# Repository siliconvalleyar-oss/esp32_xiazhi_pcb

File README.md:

# XiaoZhi - Asistente de Voz con ESP32-C6 (Versión Multisensor)

Repositorio del diseño PCB para el dispositivo **XiaoZhi**, una estación de desarrollo y asistente de voz de código abierto basado en el **ESP32-C6**. Este diseño integra audio digital de alta calidad, iluminación RGB, pantalla OLED, **pantalla TFT**, **sensores ambientales (gas, temperatura/humedad, distancia)** y **comunicación CAN** en una sola placa diseñada con **KiCad**.

---

## 📖 Descripción

XiaoZhi evoluciona para convertirse en un nodo IoT multisensor ideal para automatización del hogar, monitoreo industrial o robótica. Además de la interacción por voz (micrófono y altavoz), la placa incorpora:

- **MQ-6**: Detección de gases combustibles (LPG, butano, metano).
- **AHT21B**: Medición precisa de temperatura y humedad ambiental (I2C).
- **VL53L0X**: Sensor de distancia por tiempo de vuelo (ToF) de hasta 2 metros.
- **ST7789**: Pantalla TFT a color para gráficos avanzados (SPI).
- **MCP2515**: Controlador CAN bus (con transceptor) para comunicación vehicular o industrial.

Todo ello manteniendo la conectividad Wi-Fi 6, BLE 5.0 y la interfaz USB-UART integrada.

---

## ✨ Características Principales

- **Microcontrolador**: ESP32-C6 (RISC-V dual-core, Wi-Fi 6, BLE 5.0, Zigbee/Thread).
- **Audio**:
  - Micrófono MEMS **INMP441** (I2S).
  - Amplificador **MAX98357A** (I2S) para altavoz externo.
- **Interfaz y depuración**: **FT232** integrado para USB-UART.
- **Iluminación y control**:
  - LED GPIO estándar y LED direccionable **WS2812**.
  - Pulsadores (BOOT y RESET).
- **Pantallas**:
  - **SSD1306** (OLED 128x64, I2C) para información rápida.
  - **ST7789** (TFT a color, SPI) para gráficos, menús o visualización de datos.
- **Sensores**:
  - **MQ-6** (gas) – Salida analógica (ADC).
  - **AHT21B** (temperatura/humedad) – I2C.
  - **VL53L0X** (distancia ToF) – I2C.
- **Comunicación industrial**:
  - **MCP2515** + transceptor CAN (SPI) para bus CAN 2.0.
- **Alimentación**: 5V vía USB-C, con reguladores internos para 3.3V.

---

## 📦 Lista de Componentes (BOM)

| Componente | Cantidad | Descripción | Referencia en PCB |
| :--- | :--- | :--- | :--- |
| ESP32-C6-WROOM-1 | 1 | Módulo Wi-Fi/BLE/Zigbee | U1 |
| INMP441 | 1 | Micrófono MEMS I2S | U2 |
| MAX98357A | 1 | Amplificador Clase D I2S | U3 |
| FT232RL (o FT232RQ) | 1 | Conversor USB-UART | U4 |
| WS2812B | 1 (o N) | LED RGB direccionable | D1 |
| LED (GPIO) | 1 | LED indicador estándar | D2 |
| SWITCH (Push Button) | 2 | Pulsadores (BOOT y RESET) | SW1, SW2 |
| SSD1306 (I2C) | 1 | Display OLED de 0.96" | OLED1 |
| **MQ-6** | **1** | **Sensor de gas (LPG, butano, metano)** | **U6** |
| **AHT21B** | **1** | **Sensor de temperatura y humedad (I2C)** | **U7** |
| **VL53L0X** | **1** | **Sensor de distancia ToF (Time-of-Flight)** | **U8** |
| **ST7789** | **1** | **Pantalla TFT a color (SPI) - 1.3" / 1.54"** | **U9** |
| **MCP2515** | **1** | **Controlador CAN (SPI) + TJA1050 (transceptor)** | **U10** |
| Regulador 3.3V (AMS1117) | 1 | LDO para alimentación interna | U5 |
| Cristal 40MHz | 1 | Oscilador para FT232 (según esquema) | X1 |
| Resistencias, Capacitores, Conectores | Varios | Pasivos y terminales (USB-C, JST) | - |

---

## 🔌 Asignación de Pines (Pinout)

> **⚠️ Importante**: La siguiente tabla es una referencia estándar. Verifica siempre el esquemático (`*.sch`) para confirmar las conexiones finales.

| Periférico | Pin del ESP32-C6 | Descripción / Notas |
| :--- | :--- | :--- |
| **INMP441 (Mic)** | GPIO3 (I2S_BCK) | Bit Clock |
| | GPIO2 (I2S_WS) | Word Select (LRCLK) |
| | GPIO1 (I2S_DIN) | Data Output (DOUT) |
| | 3.3V / GND | Alimentación |
| **MAX98357A (Amp)** | GPIO3 (I2S_BCK) | Bit Clock (compartido) |
| | GPIO2 (I2S_WS) | Word Select (compartido) |
| | GPIO4 (I2S_DOUT) | Data Input (DIN) |
| | GPIO5 | Shutdown (SD) - Activo bajo |
| | 5V / GND | Alimentación |
| **WS2812** | GPIO6 | Data Input |
| | 5V / GND | Alimentación |
| **SSD1306 (OLED) / AHT21B / VL53L0X** | GPIO7 (I2C_SCL) | Bus I2C compartido (SCL) |
| | GPIO8 (I2C_SDA) | Bus I2C compartido (SDA) |
| | 3.3V / GND | Alimentación (todas comparten bus) |
| **FT232 (UART)** | GPIO9 (RX) | RX del ESP (conectar a TX del FT) |
| | GPIO10 (TX) | TX del ESP (conectar a RX del FT) |
| | GPIO11 (DTR) | Auto-reset (opcional) |
| **SWITCH BOOT** | GPIO12 | Boot (GPIO0 en otros chips, verificar) |
| **SWITCH RESET** | CHIP_EN | Reset (EN) |
| **LED GPIO** | GPIO13 | Ánodo del LED (con resistencia) |
| **MQ-6 (Gas)** | **GPIO14** | **Salida analógica (ADC)** |
| **ST7789 (TFT)** | **GPIO15 (SPI_MOSI)** | **Master Out / Slave In** |
| | **GPIO16 (SPI_SCLK)** | **Clock SPI** |
| | **GPIO17 (DC)** | **Data/Command** |
| | **GPIO18 (CS)** | **Chip Select (activo bajo)** |
| | **GPIO19 (RST)** | **Reset de la pantalla** |
| **MCP2515 (CAN)** | **GPIO15 (SPI_MOSI)** | **Comparte MOSI con TFT** |
| | **GPIO16 (SPI_SCLK)** | **Comparte SCLK con TFT** |
| | **GPIO20 (CS)** | **Chip Select exclusivo para CAN** |
| | **GPIO21 (INT)** | **Interrupción del MCP2515** |
| | 5V / GND | Alimentación (transceptor CAN) |

---

## 🧩 Integración de Sensores y Bus Compartido

Para optimizar los pines del ESP32-C6, el diseño utiliza buses compartidos:

- **Bus I2C (GPIO7 y GPIO8)**: Conecta simultáneamente el **SSD1306**, el **AHT21B** y el **VL53L0X**. Cada dispositivo tiene una dirección I2C única, por lo que no hay conflicto.
- **Bus SPI (GPIO15 y GPIO16)**: Conecta el **ST7789** y el **MCP2515**. Se diferencian mediante pines **CS (Chip Select)** independientes (GPIO18 para TFT, GPIO20 para CAN).
- **ADC (GPIO14)**: Reservado exclusivamente para la salida analógica del sensor de gas **MQ-6**. Se recomienda agregar un capacitor de filtrado en la PCB para estabilizar la lectura.

---

## 🛠️ Uso del Proyecto en KiCad

### Requisitos
- KiCad **v8.0** o superior.
- Símbolos y huellas adicionales para los nuevos componentes (es posible que necesites descargar librerías externas para el MCP2515, VL53L0X o ST7789).

### Abrir y Editar
1. Clona este repositorio:
   ```bash
   git clone https://github.com/tu-usuario/xiaozhi-pcb.git
   cd xiaozhi-pcb

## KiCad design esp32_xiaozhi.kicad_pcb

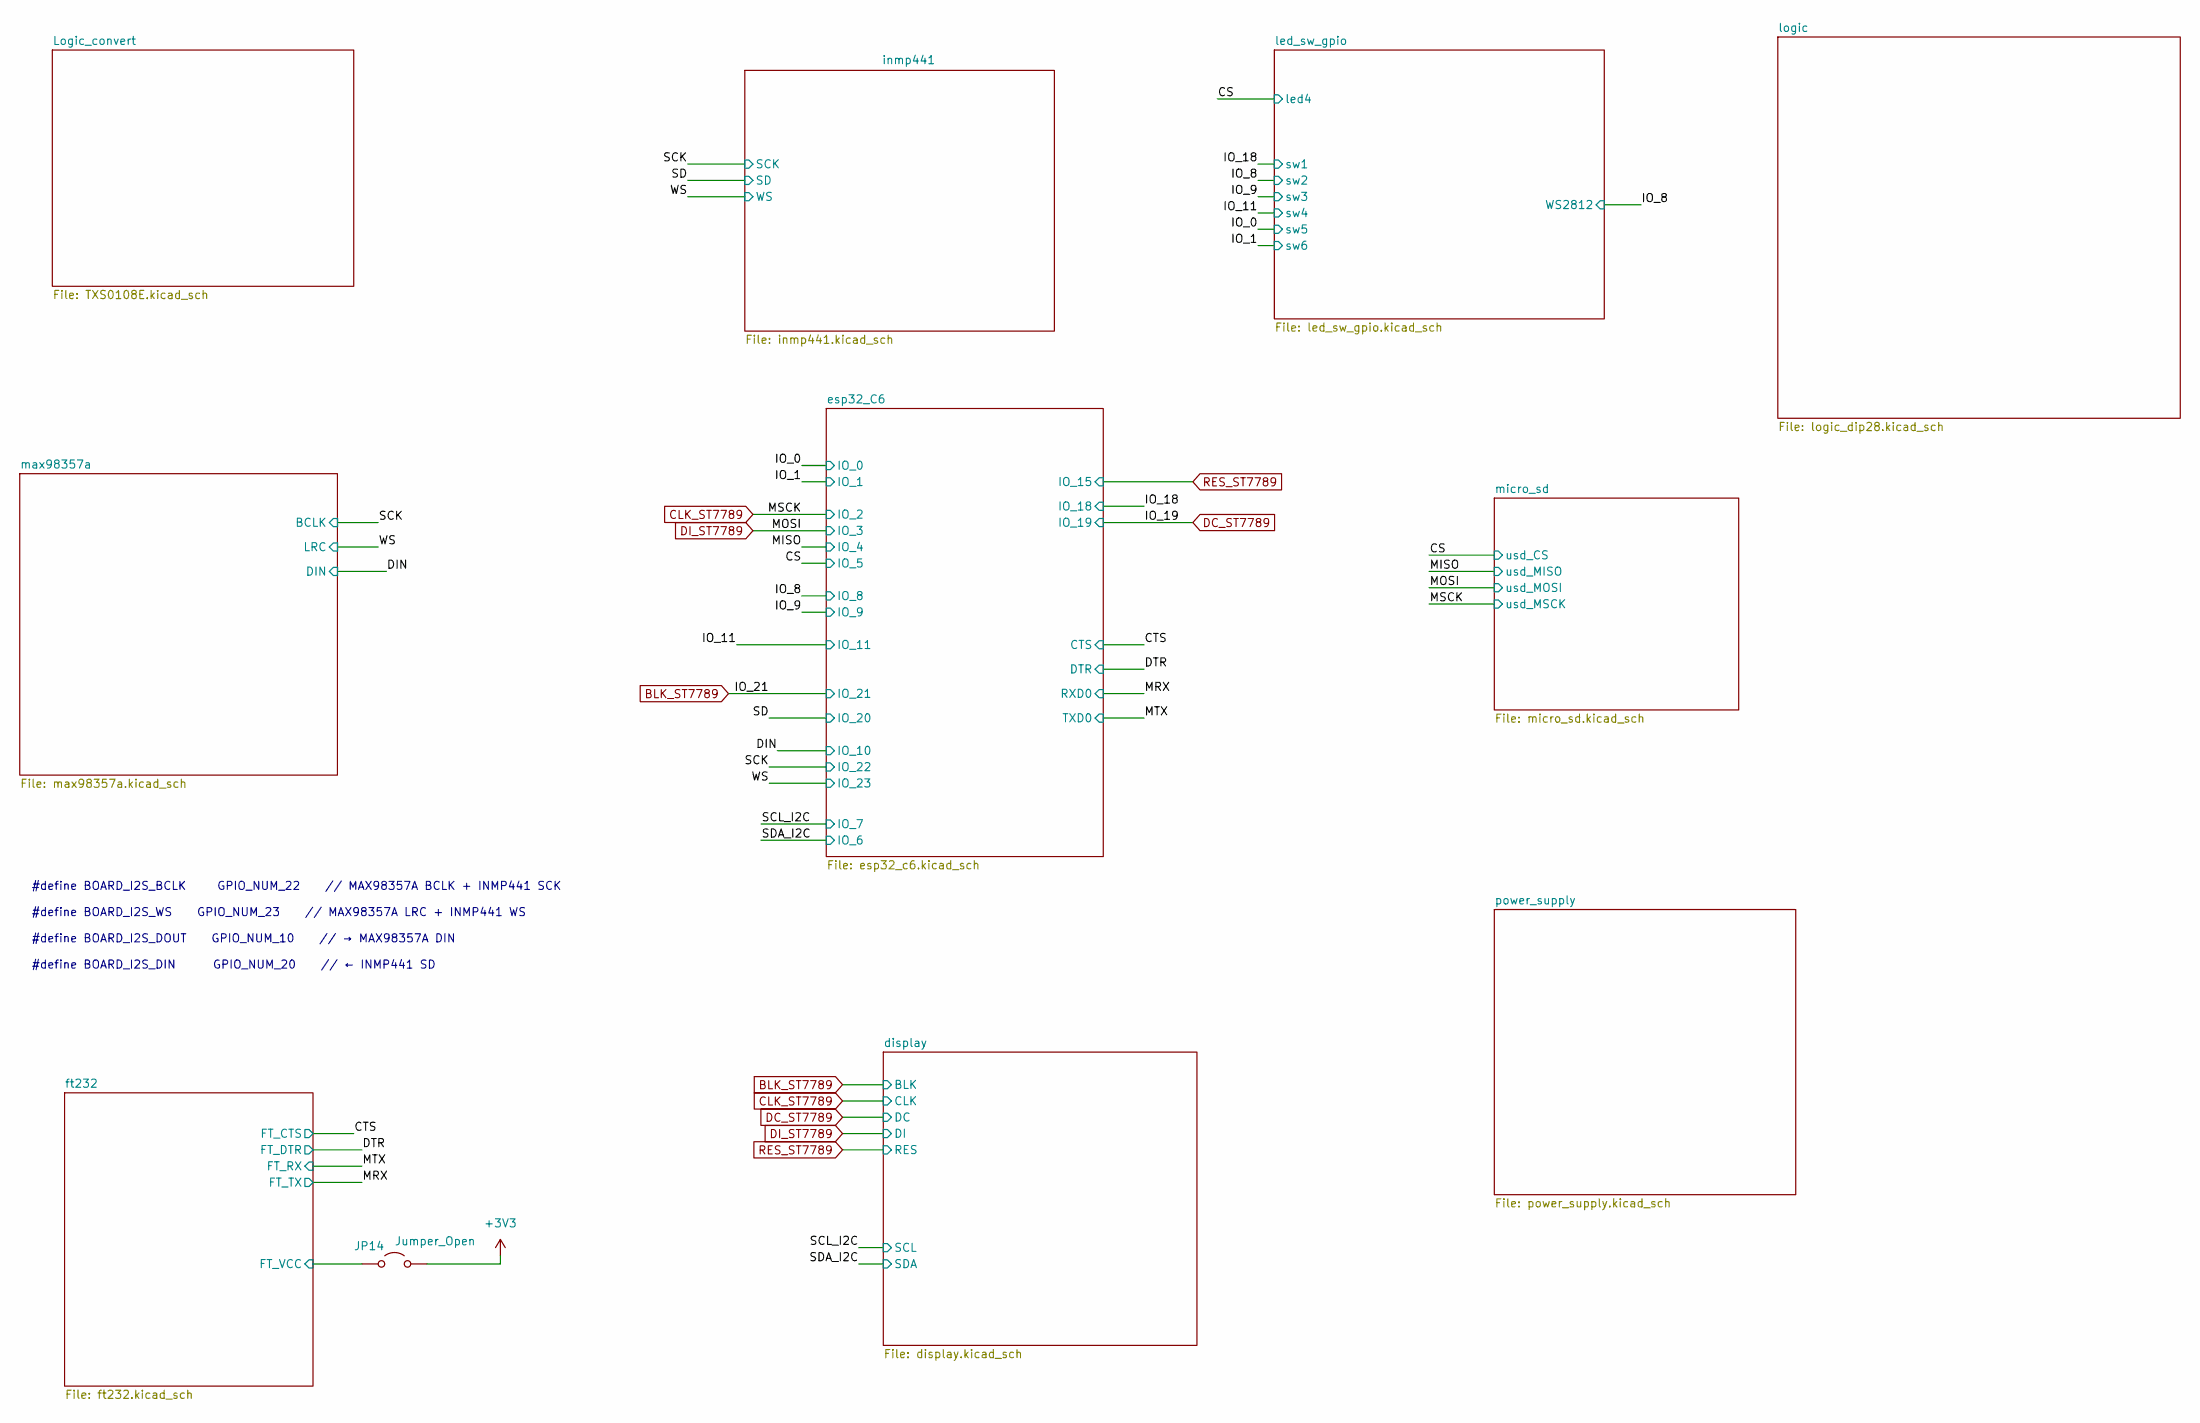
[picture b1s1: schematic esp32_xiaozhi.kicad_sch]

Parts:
JP14: Jumper_Open; SolderJumper-2_P1.3mm_Open_RoundedPad1.0x1.5mm

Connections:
+3V3: JP14.2 (B); also elsewhere on the board
+5VA: JP14.1 (A); also elsewhere on the board

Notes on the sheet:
#define BOARD_I2S_BCLK GPIO_NUM_22 // MAX98357A BCLK + INMP441 SCK #define BOARD_I2S_WS GPIO_NUM_23 // MAX98357A LRC + INMP441 WS #define BOARD_I2S_DOUT GPIO_NUM_10 // → MAX98357A DIN #define BOARD_I2S_DIN GPIO_NUM_20 // ← INMP441 SD

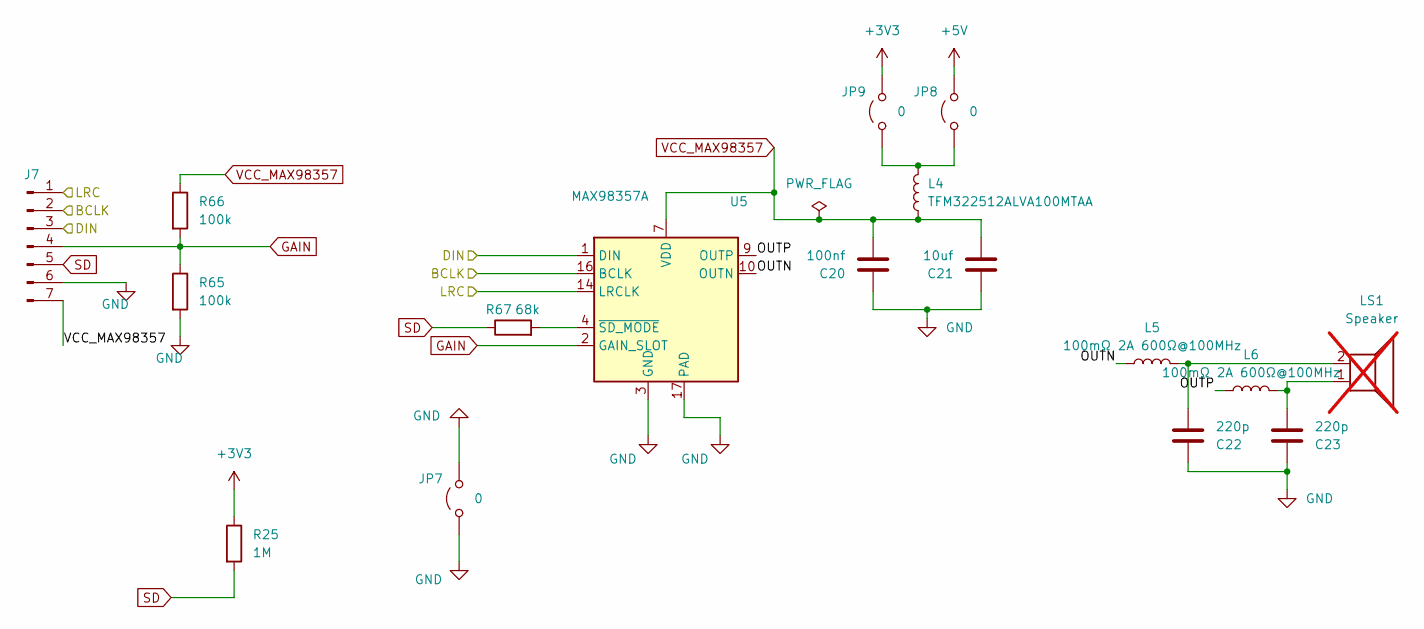
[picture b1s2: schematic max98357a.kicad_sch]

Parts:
C20: 100nf; C_0805_2012Metric; LCSC C28233
C21: 10uf; C_0805_2012Metric; LCSC C15850
C22, C23: 220p; C_0805_2012Metric; LCSC C107145
J7: PinHeader_1x07_P2.54mm_Vertical
JP7, JP8: 0; SolderJumper-2_P1.3mm_Bridged_RoundedPad1.0x1.5mm
JP9: 0; SolderJumper-2_P1.3mm_Open_RoundedPad1.0x1.5mm
L4: TFM322512ALVA100MTAA; L_1210_3225Metric; LCSC C1882517
L5, L6: 100mΩ 2A 600Ω@100MHz; L_0805_2012Metric; LCSC C845118
LS1: Speaker; Molex_Micro-Latch_53253-0270_1x02_P2.00mm_Vertical; not fitted
R25: 1M; R_0805_2012Metric; LCSC C17514
R65, R66: 100k; R_0805_2012Metric; LCSC C149504
R67: 68k; R_0805_2012Metric; LCSC C17801
U5: MAX98357A; TQFN-16-1EP_3x3mm_P0.5mm_EP1.23x1.23mm; LCSC C910544

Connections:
+3V3: JP9.2 (B), R25.1; also elsewhere on the board
+5V: JP8.2 (B); also elsewhere on the board
/DIN: J7.3, U5.1 (DIN); also elsewhere on the board
/SCK: J7.2, U5.16 (BCLK); also elsewhere on the board
/WS: J7.1, U5.14 (LRCLK); also elsewhere on the board
/max98357a/OUTN: L5.1, U5.10 (OUTN)
/max98357a/OUTP: L6.1, U5.9 (OUTP)
GAIN: J7.4, R65.1, R66.2, U5.2 (GAIN_SLOT)
unnamed: C22.2, L5.2, LS1.2
unnamed: C23.2, L6.2, LS1.1
unnamed: JP8.1 (A), JP9.1 (A), L4.2
unnamed: R67.2, U5.4 (~SD_MODE)
SD: J7.5, R25.2, R67.1
VCC_MAX98357: C20.2, C21.2, J7.7, L4.1, R66.1, U5.7 (VDD), U5.8 (VDD)

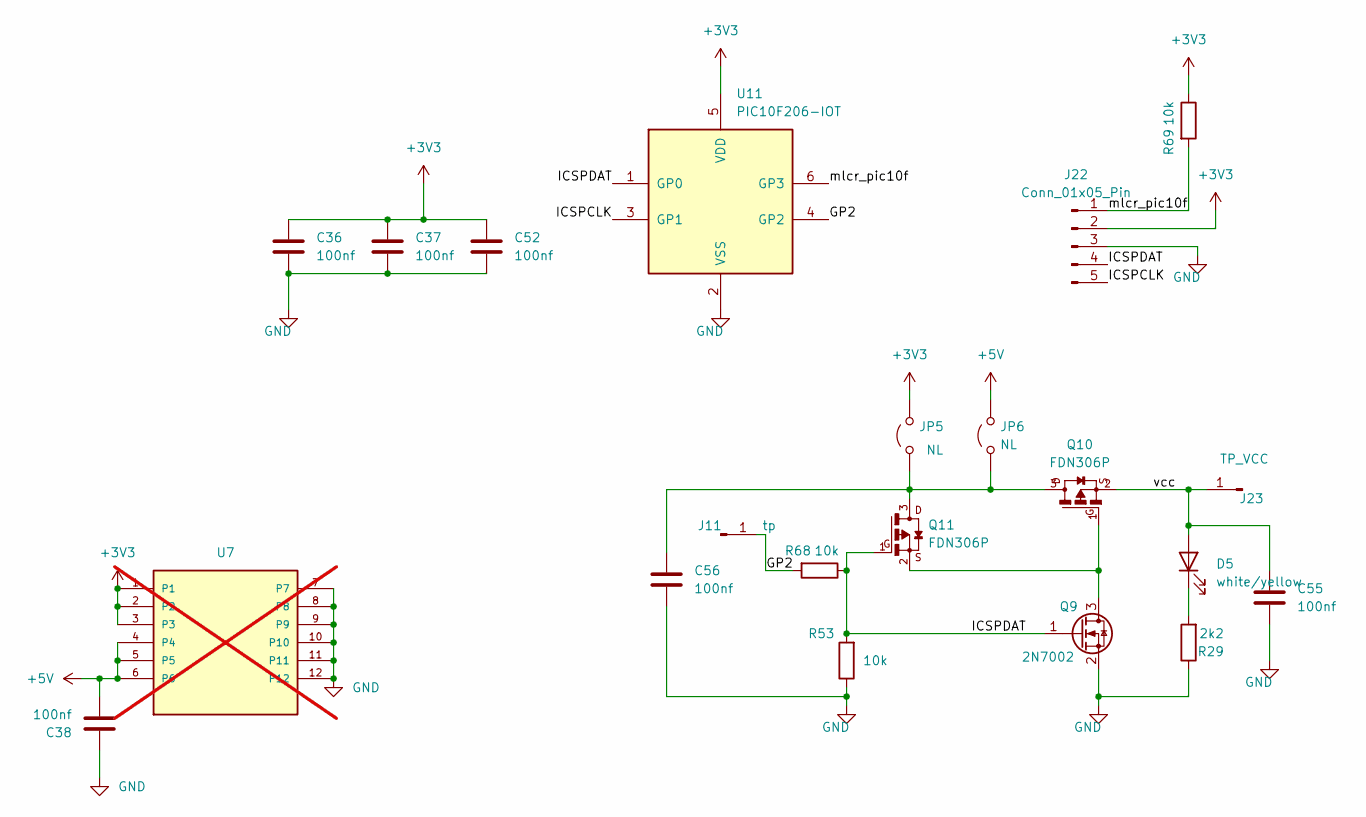
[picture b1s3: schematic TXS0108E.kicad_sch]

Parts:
C36, C37, C38, C52, C55, C56: 100nf; C_0805_2012Metric; LCSC C28233
D5: white/yellow; D_0805_2012Metric; LCSC C34499
J11: tp; TestPoint_Pad_D1.5mm
J22: Conn_01x05_Pin; PinHeader_1x06_P1.00mm_Vertical_SMD_Pin1Left
J23: TP_VCC; TestPoint_THTPad_1.0x1.0mm_Drill0.5mm
JP5, JP6: NL; SolderJumper-2_P1.3mm_Open_RoundedPad1.0x1.5mm
Q9: 2N7002; SOT-23; LCSC C8545
Q10, Q11: FDN306P; SOT-23W; LCSC C5236682
R29: 2k2; R_0805_2012Metric; LCSC C17520
R53, R68, R69: 10k; R_0805_2012Metric; LCSC C17414
U7: FMINI_PB_6X6; not fitted
U11: PIC10F206-IOT; SOT-23-6; LCSC C220623

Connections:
+3V3: C36.1, C37.1, C52.1, J22.2, JP5.2 (B), R69.1, U7.1, U7.2, U7.3, U11.5 (VDD); also elsewhere on the board
+5V: C38.2, JP6.2 (B), U7.4, U7.5, U7.6; also elsewhere on the board
/Logic_convert/GP2: J11.1 (Pin_1_1), R68.2, U11.4 (GP2)
/Logic_convert/ICSPCLK: J22.5, U11.3 (GP1)
/Logic_convert/ICSPDAT: J22.4, Q9.1 (G), Q11.1, R53.2, R68.1, U11.1 (GP0)
/Logic_convert/mlcr_pic10f: J22.1, R69.2, U11.6 (GP3)
/Logic_convert/vcc: C55.1, D5.2 (A), J23.1 (Pin_1_1), Q10.2
unnamed: D5.1 (K), R29.2
unnamed: C56.1, JP5.1 (A), JP6.1 (A), Q10.3, Q11.3
unnamed: Q9.3 (D), Q10.1, Q11.2

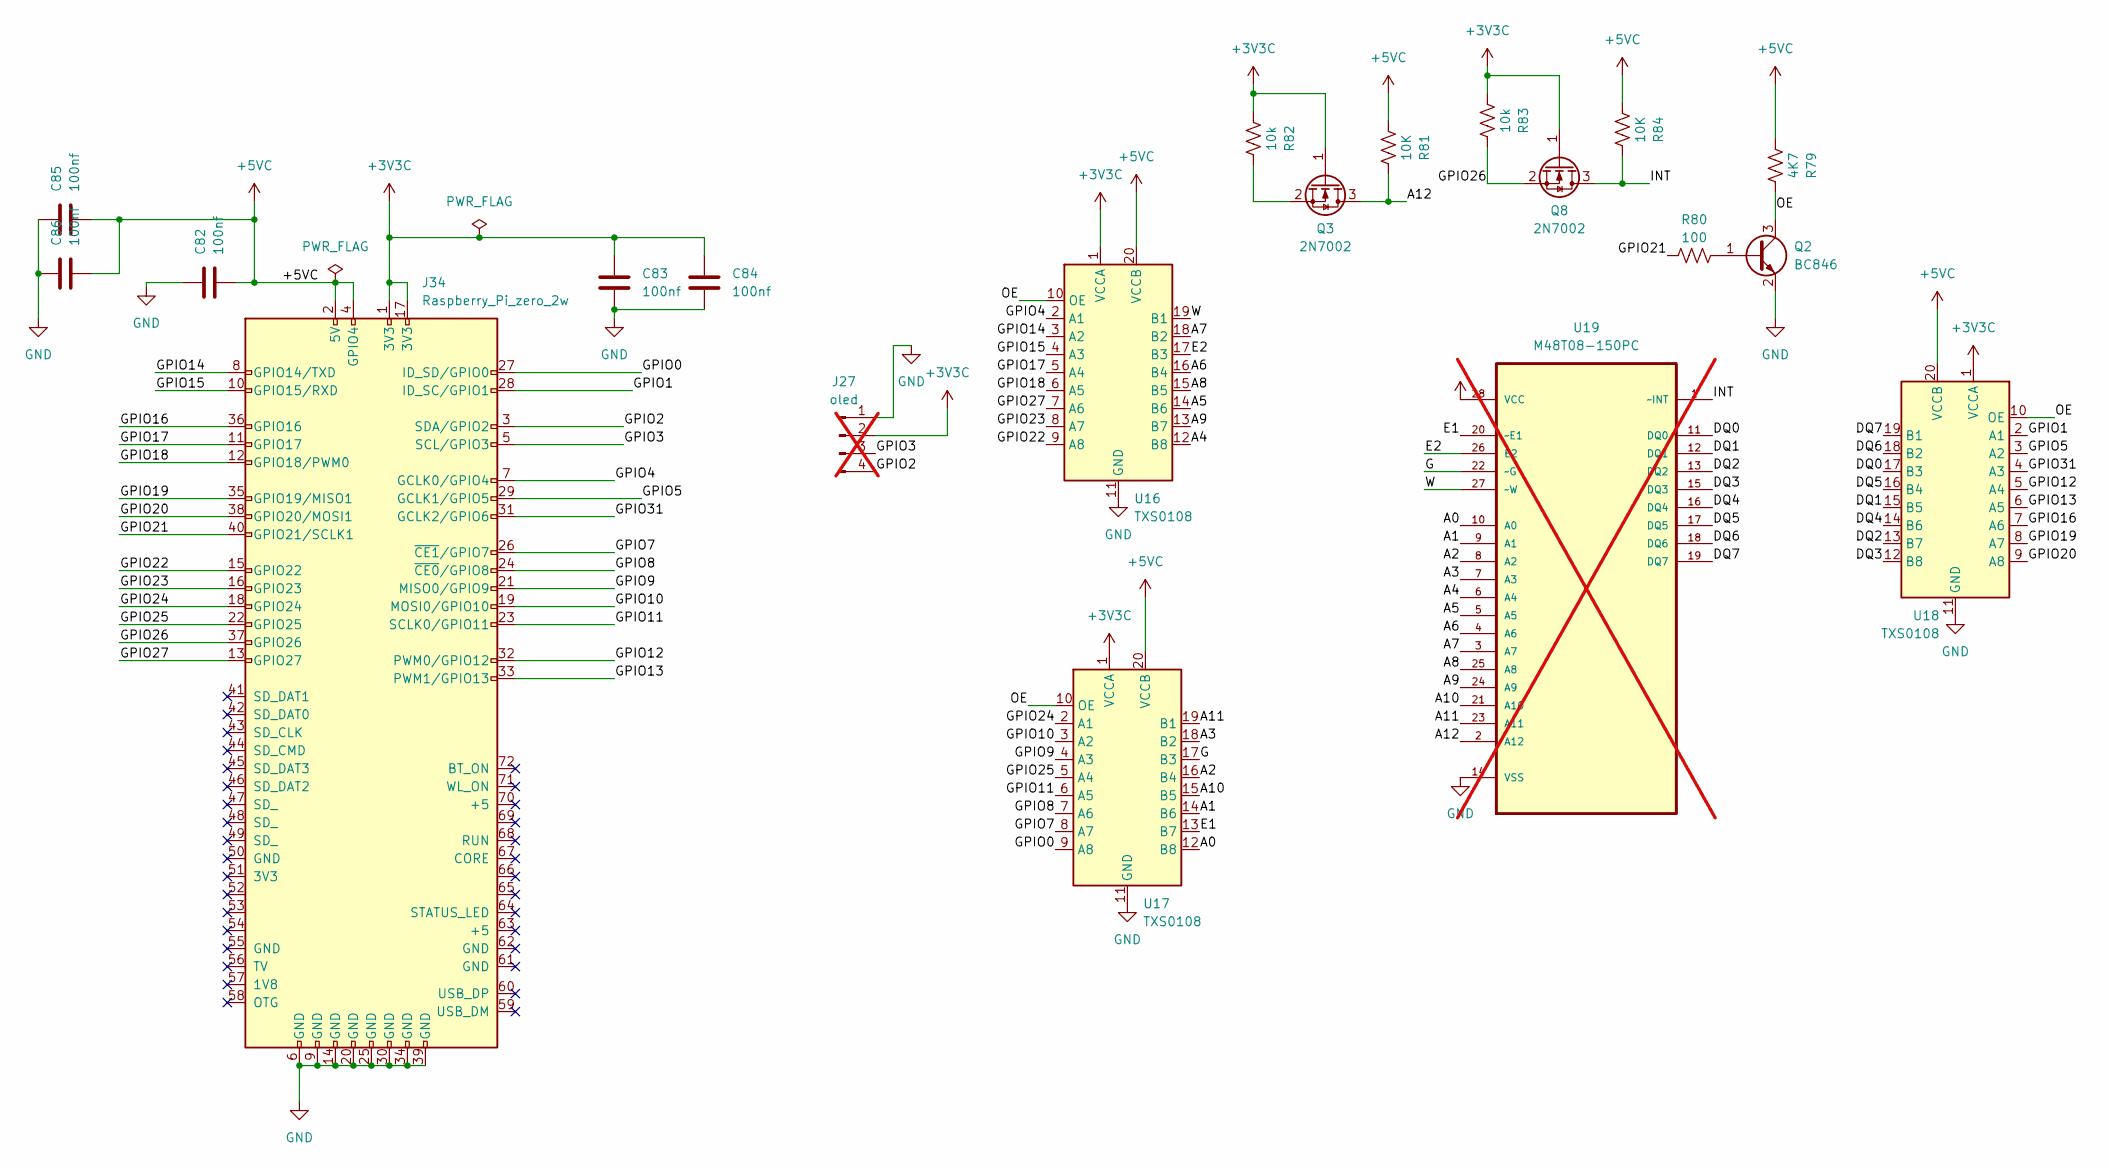
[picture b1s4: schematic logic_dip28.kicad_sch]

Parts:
C82, C85, C86: 100nf; C_0805_2012Metric
C83, C84: 100nf; C_0603_1608Metric
J27: oled; PinHeader_1x04_P2.54mm_Vertical; not fitted
J34: Raspberry_Pi_zero_2w; PinSocket_2x20_P2.54mm_Vertical_SMD
Q2: BC846; SOT-23
Q3, Q8: 2N7002; SOT-23
R79: 4K7; R_0603_1608Metric
R80: 100; R_0603_1608Metric
R81, R84: 10K; R_0603_1608Metric
R82, R83: 10k; R_0603_1608Metric
U16, U17, U18: TXS0108; TSSOP-20_4.4x6.5mm_P0.65mm
U19: M48T08-150PC; DIP-28_W15.24mm; MPN M48T08-150PC; not fitted

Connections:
+3V3C: C83.1, C84.1, J27.2, J34.1 (3V3), J34.17 (3V3), Q3.1 (G), Q8.1 (G), R82.1, R83.1, U16.1 (VCCA), U17.1 (VCCA), U18.1 (VCCA)
+5VC: C82.2, C85.2, C86.2, J34.2 (5V), J34.4 (GPIO4), R79.1, R81.1, R84.1, U16.20 (VCCB), U17.20 (VCCB), U18.20 (VCCB), U19.28 (VCC)
/logic/A0: U17.12 (B8), U19.10 (A0)
/logic/A1: U17.14 (B6), U19.9 (A1)
/logic/A2: U17.16 (B4), U19.8 (A2)
/logic/A3: U17.18 (B2), U19.7 (A3)
/logic/A4: U16.12 (B8), U19.6 (A4)
/logic/A5: U16.14 (B6), U19.5 (A5)
/logic/A6: U16.16 (B4), U19.4 (A6)
/logic/A7: U16.18 (B2), U19.3 (A7)
/logic/A8: U16.15 (B5), U19.25 (A8)
/logic/A9: U16.13 (B7), U19.24 (A9)
/logic/A10: U17.15 (B5), U19.21 (A10)
/logic/A11: U17.19 (B1), U19.23 (A11)
/logic/A12: Q3.3 (D), R81.2, U19.2 (A12)
/logic/DQ0: U18.17 (B3), U19.11 (DQ0)
/logic/DQ1: U18.15 (B5), U19.12 (DQ1)
/logic/DQ2: U18.13 (B7), U19.13 (DQ2)
/logic/DQ3: U18.12 (B8), U19.15 (DQ3)
/logic/DQ4: U18.14 (B6), U19.16 (DQ4)
/logic/DQ5: U18.16 (B4), U19.17 (DQ5)
/logic/DQ6: U18.18 (B2), U19.18 (DQ6)
/logic/DQ7: U18.19 (B1), U19.19 (DQ7)
/logic/E1: U17.13 (B7), U19.20 (~E1)
/logic/E2: U16.17 (B3), U19.26 (E2)
/logic/G: U17.17 (B3), U19.22 (~G)
/logic/GPIO0: J34.27 (ID_SD/GPIO0), U17.9 (A8)
/logic/GPIO1: J34.28 (ID_SC/GPIO1), U18.2 (A1)
/logic/GPIO2: J27.4, J34.3 (SDA/GPIO2)
/logic/GPIO3: J27.3, J34.5 (SCL/GPIO3)
/logic/GPIO4: J34.7 (GCLK0/GPIO4), U16.2 (A1)
/logic/GPIO5: J34.29 (GCLK1/GPIO5), U18.3 (A2)
/logic/GPIO7: J34.26 (~CE1/GPIO7), U17.8 (A7)
/logic/GPIO8: J34.24 (~CE0/GPIO8), U17.7 (A6)
/logic/GPIO9: J34.21 (MISO0/GPIO9), U17.4 (A3)
/logic/GPIO10: J34.19 (MOSI0/GPIO10), U17.3 (A2)
/logic/GPIO11: J34.23 (SCLK0/GPIO11), U17.6 (A5)
/logic/GPIO12: J34.32 (PWM0/GPIO12), U18.5 (A4)
/logic/GPIO13: J34.33 (PWM1/GPIO13), U18.6 (A5)
/logic/GPIO14: J34.8 (GPIO14/TXD), U16.3 (A2)
/logic/GPIO15: J34.10 (GPIO15/RXD), U16.4 (A3)
/logic/GPIO16: J34.36 (GPIO16), U18.7 (A6)
/logic/GPIO17: J34.11 (GPIO17), U16.5 (A4)
/logic/GPIO18: J34.12 (GPIO18/PWM0), U16.6 (A5)
/logic/GPIO19: J34.35 (GPIO19/MISO1), U18.8 (A7)
/logic/GPIO20: J34.38 (GPIO20/MOSI1), U18.9 (A8)
/logic/GPIO21: J34.40 (GPIO21/SCLK1), R80.1
/logic/GPIO22: J34.15 (GPIO22), U16.9 (A8)
/logic/GPIO23: J34.16 (GPIO23), U16.8 (A7)
/logic/GPIO24: J34.18 (GPIO24), U17.2 (A1)
/logic/GPIO25: J34.22 (GPIO25), U17.5 (A4)
/logic/GPIO26: J34.37 (GPIO26), Q8.2 (S), R83.2
/logic/GPIO27: J34.13 (GPIO27), U16.7 (A6)
/logic/GPIO31: J34.31 (GCLK2/GPIO6), U18.4 (A3)
/logic/INT: Q8.3 (D), R84.2, U19.1 (~INT)
/logic/OE: Q2.3 (C), R79.2, U16.10 (OE), U17.10 (OE), U18.10 (OE)
/logic/W: U16.19 (B1), U19.27 (~W)
unnamed: Q2.1 (B), R80.2
unnamed: Q3.2 (S), R82.2

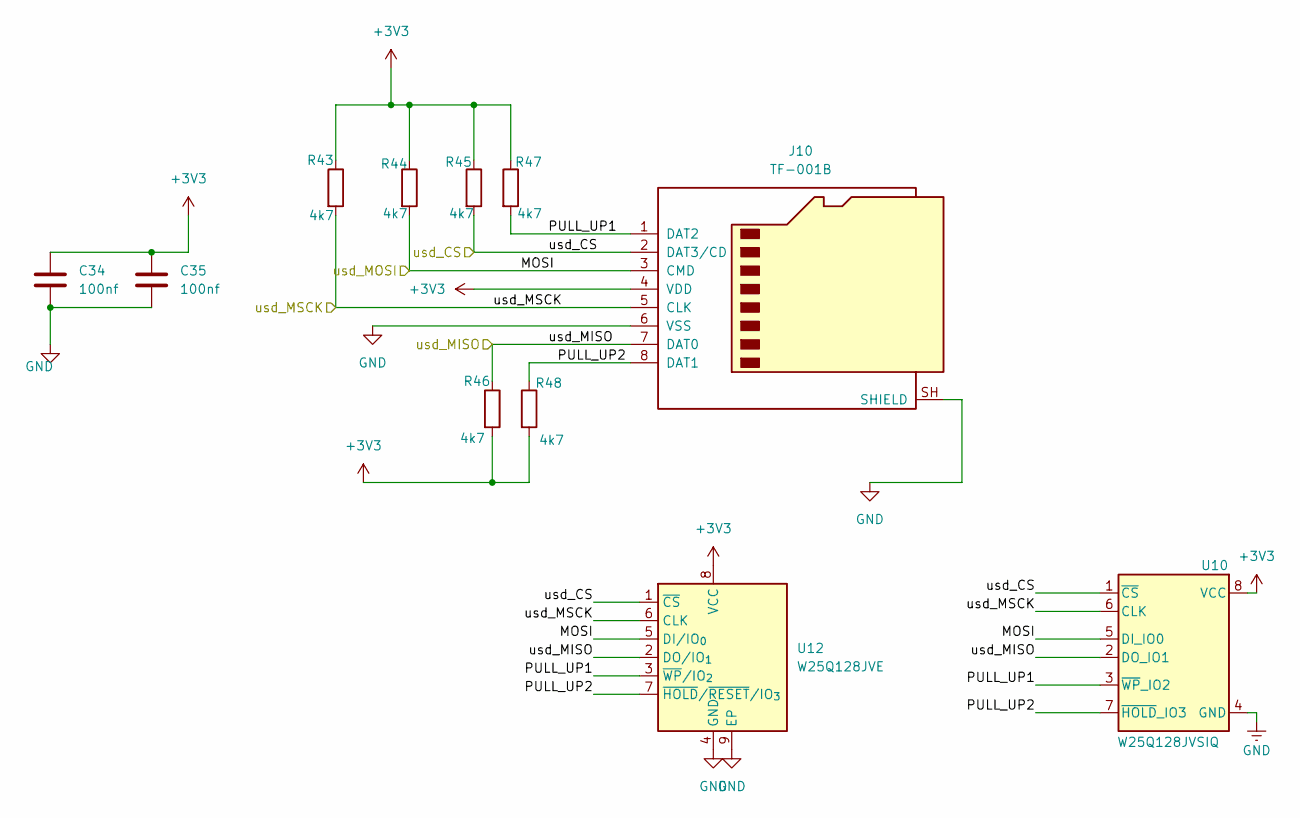
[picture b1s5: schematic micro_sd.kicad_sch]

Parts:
C34, C35: 100nf; C_0805_2012Metric; LCSC C28233
J10: TF-001B; LCSC C125617
R43, R44, R45, R46, R47, R48: 4k7; R_0805_2012Metric; LCSC C17673
U10: W25Q128JVSIQ; SOIC-8W_5.3x5.3mm_P1.27mm; voltage 2.7-3.6V; part_uid RP-01JWD4-F1H4N9; LCSC C97521
U12: W25Q128JVE; Winbond_XSON-8-1EP_4x4mm_P0.8mm_EP2.3x3.0mm

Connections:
+3V3: C34.1, C35.1, J10.4 (VDD), R43.1, R44.1, R45.1, R46.2, R47.1, R48.2, U10.8 (VCC), U12.8 (VCC); also elsewhere on the board
/CS: J10.2 (DAT3/CD), R45.2, U10.1 (~CS), U12.1 (~CS); also elsewhere on the board
/MISO: J10.7 (DAT0), R46.1, U10.2 (DO_IO1), U12.2 (DO/IO_{1}); also elsewhere on the board
/micro_sd/PULL_UP1: J10.1 (DAT2), R47.2, U10.3 (~WP_IO2), U12.3 (~WP/IO_{2})
/micro_sd/PULL_UP2: J10.8 (DAT1), R48.1, U10.7 (~HOLD_IO3), U12.7 (~HOLD/~RESET/IO_{3})
CLK_ST7789: J10.5 (CLK), R43.2, U10.6 (CLK), U12.6 (CLK); also elsewhere on the board
DI_ST7789: J10.3 (CMD), R44.2, U10.5 (DI_IO0), U12.5 (DI/IO_{0}); also elsewhere on the board

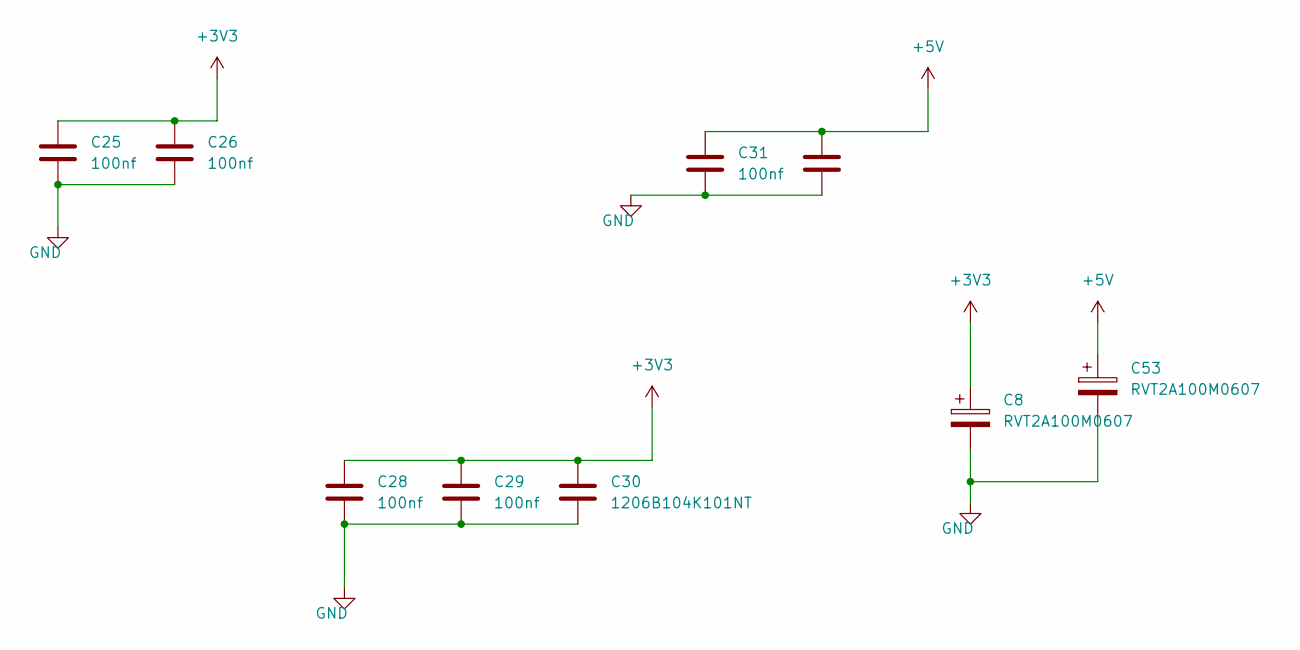
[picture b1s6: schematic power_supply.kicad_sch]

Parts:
C8, C53: RVT2A100M0607; C_Elec_6.3x7.7; LCSC C48587228
C25, C26, C28, C29, C31: 100nf; C_1206_3216Metric; LCSC C110255
C30: 1206B104K101NT; C_1206_3216Metric; LCSC C110255
C32: 1uf; C_1206_3216Metric; LCSC C1848

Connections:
+3V3: C8.1, C25.1, C26.1, C28.1, C29.1, C30.1; also elsewhere on the board
+5V: C31.1, C32.1, C53.1; also elsewhere on the board

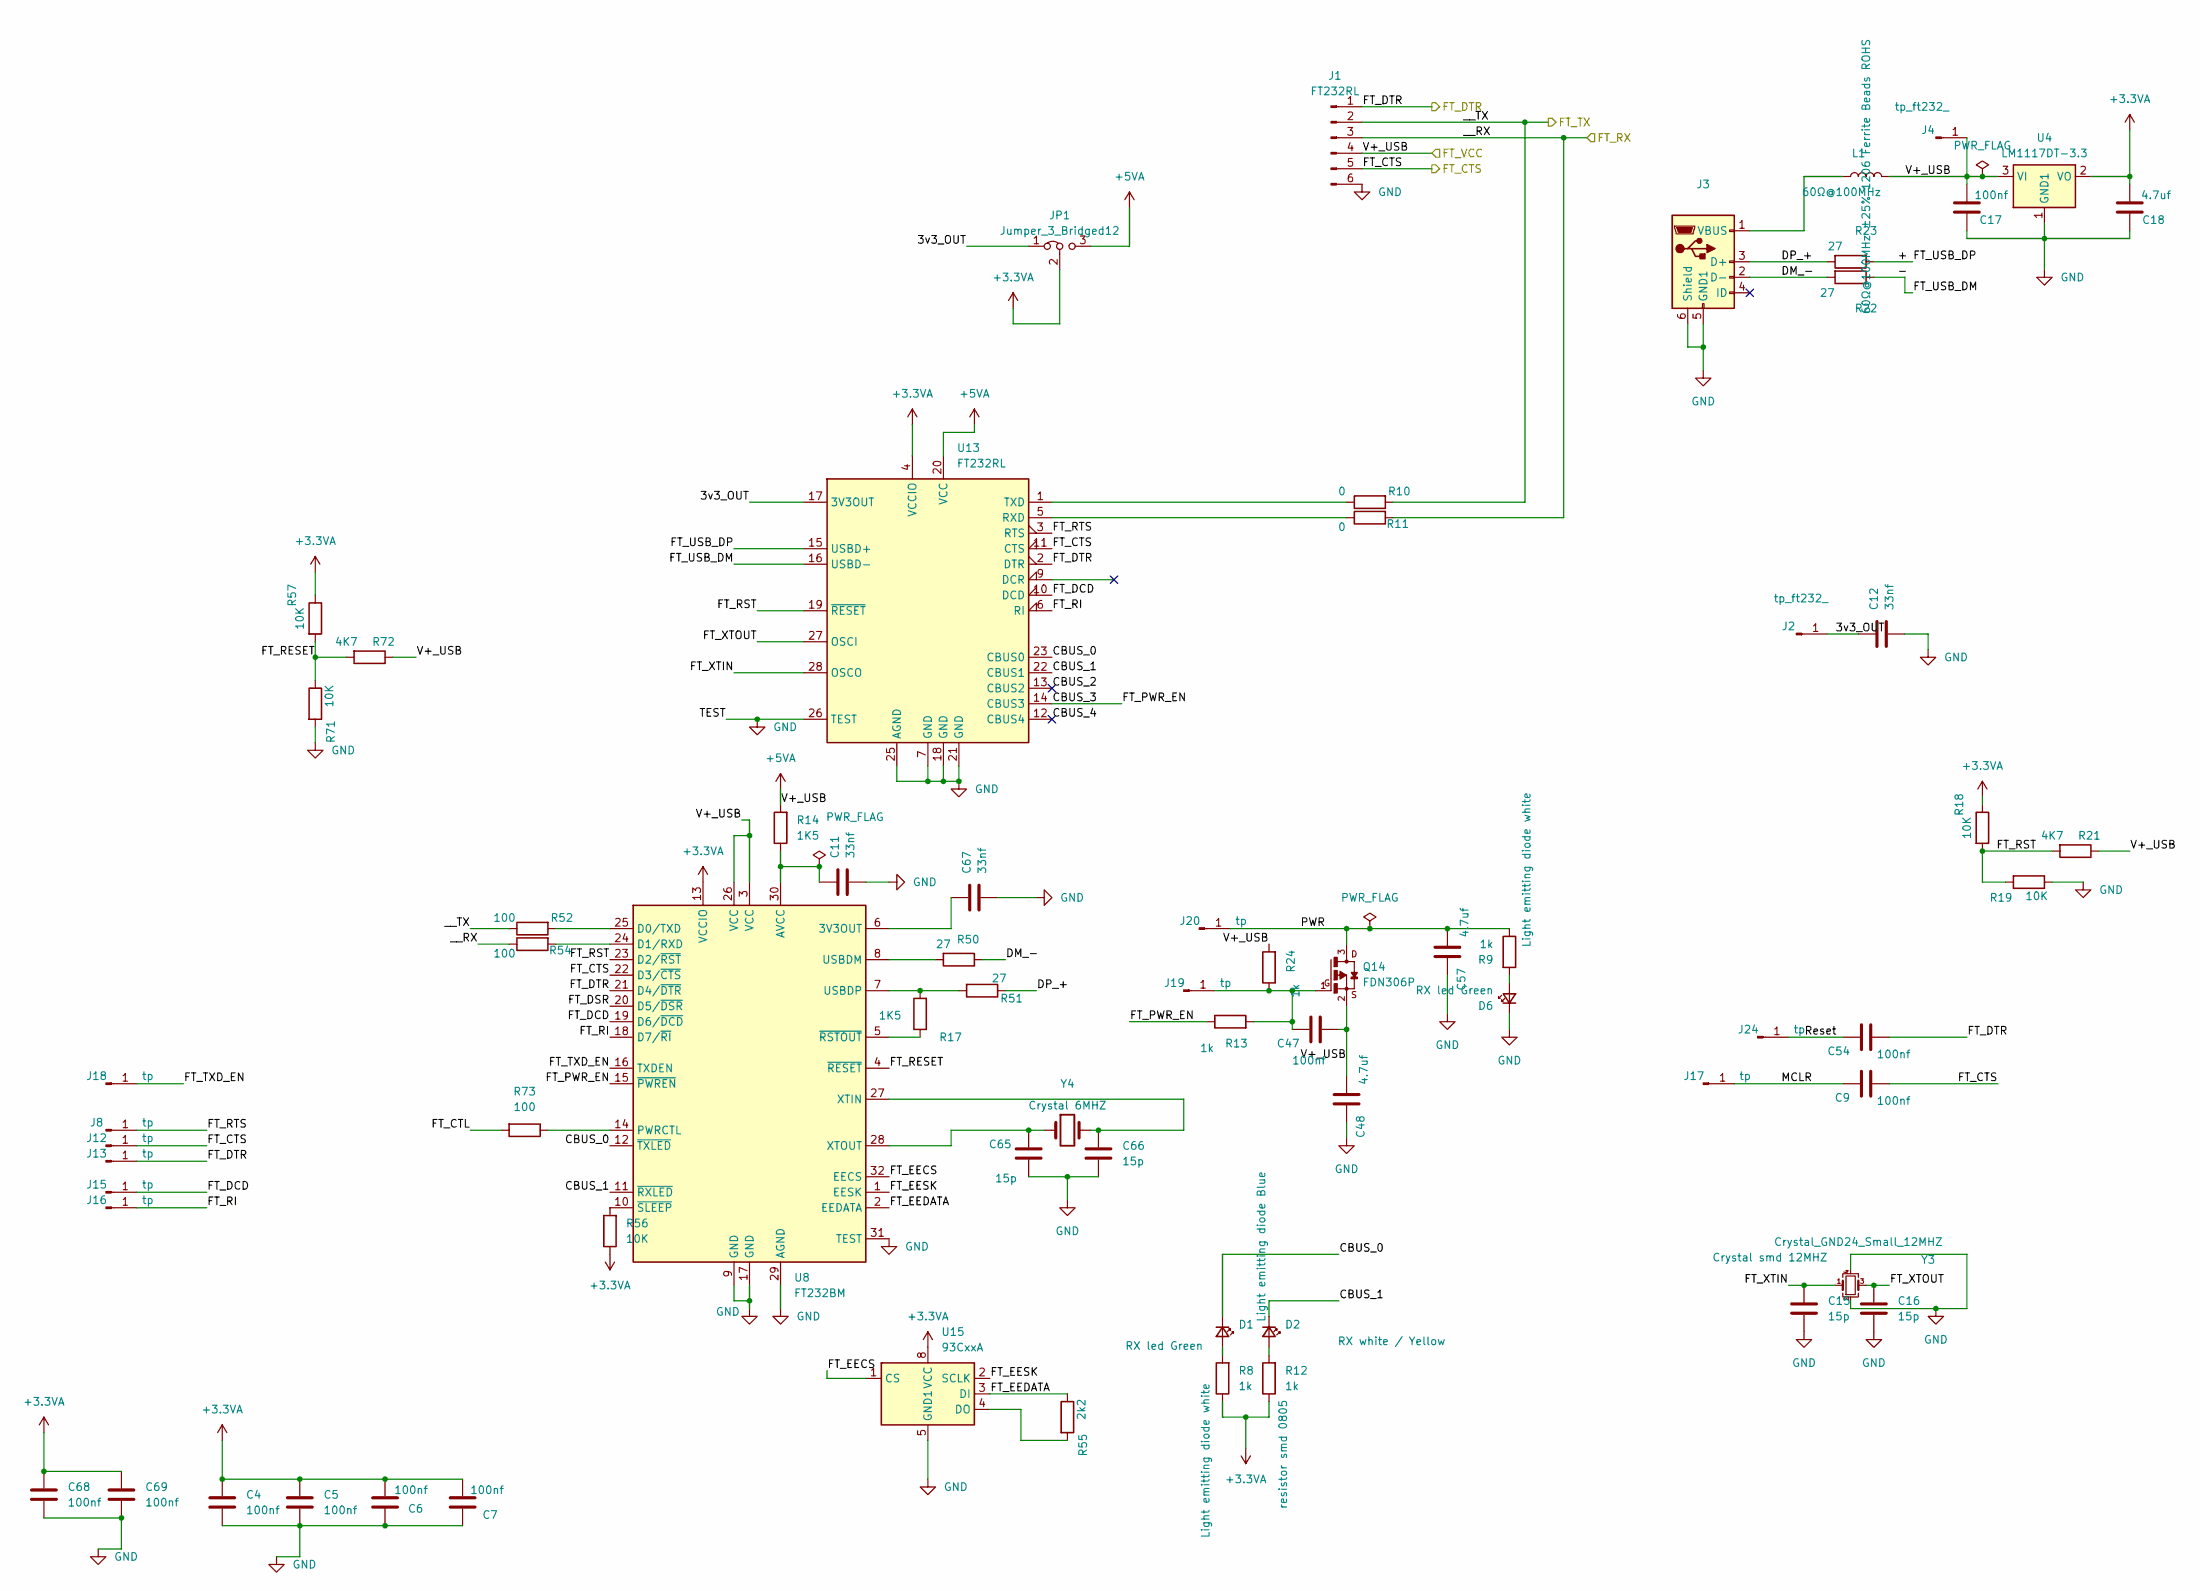
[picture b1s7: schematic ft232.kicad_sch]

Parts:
C4, C5, C6, C7, C9, C17, C47, C54, C68, C69: 100nf; C_0805_2012Metric; LCSC C28233
C11, C12, C67: 33nf; C_0805_2012Metric; LCSC C1739
C15, C16, C65, C66: 15p; C_0805_2012Metric; LCSC C107110
C18, C48, C57: 4.7uf; C_0805_2012Metric; LCSC C1779
D1, D6: RX led Green; D_0805_2012Metric; LCSC C2297
D2: RX white / Yellow; D_0805_2012Metric; LCSC C34499
J1: FT232RL; PinHeader_1x06_P2.54mm_Vertical
J2, J4: tp_ft232_; TestPoint_THTPad_1.0x1.0mm_Drill0.5mm
J3: U-M-M5SS-W-2; USB_Mini-B_Lumberg_2486_01_Horizontal; LCSC C91144
J8, J12, J13, J15, J16, J17, J18, J19, J20, J24: tp; TestPoint_THTPad_1.0x1.0mm_Drill0.5mm
JP1: Jumper_3_Bridged12; SolderJumper-3_P1.3mm_Bridged12_Pad1.0x1.5mm
L1: 60Ω@100MHz; L_1206_3216Metric; LCSC C74489
Q14: FDN306P; SOT-23W; LCSC C5236682
R8, R9, R12, R13, R24: 1k; R_0805_2012Metric; LCSC C17513
R10, R11: 0; R_0805_2012Metric; LCSC C17477
R14, R17: 1K5; R_0805_2012Metric; LCSC C4310
R18, R19: 10K; R_0805_2012Metric; LCSC C17414
R21: 4K7; R_0805_2012Metric; LCSC C17673
R22, R23, R50, R51: 27; R_0805_2012Metric; LCSC C2933393
R52, R54: 100; R_0805_2012Metric; LCSC C17477
R55: 2k2; R_0805_2012Metric
R56, R57, R71: 10K; R_0805_2012Metric
R72: 4K7; R_0805_2012Metric
R73: 100; R_0805_2012Metric
U4: LM1117DT-3.3; SOT-223-3_TabPin2; LCSC C9662
U8: FT232BM; LQFP-32_7x7mm_P0.8mm
U13: FT232RL; SSOP-28_5.3x10.2mm_P0.65mm; LCSC C8690
U15: 93CxxA; SOIC-8_7.5x5.85mm_P1.27mm
Y3: Crystal_GND24_Small_12MHZ; Oscillator_SMD_Abracon_ASE-4Pin_3.2x2.5mm; LCSC C20625731
Y4: Crystal 6MHZ; Crystal_SMD_HC49-SD

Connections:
+3.3VA: C4.1, C5.1, C6.2, C7.2, C18.2, C68.1, C69.1, JP1.2 (C), R8.1, R12.1, R18.1, R56.1, R57.1, U4.2 (VO), U8.13 (VCCIO), U13.4 (VCCIO), U15.8 (VCC)
+5VA: C17.2, C47.2, C48.2, J1.4, J4.1 (Pin_1_1), JP1.3 (B), L1.2, Q14.2, R14.2, R21.1, R24.2, R72.1, U4.3 (VI), U8.3 (VCC), U8.26 (VCC), U13.20 (VCC); also elsewhere on the board
/CTS: C9.2, J1.5, J12.1 (Pin_1_1), U8.22 (D3/~CTS), U13.11 (CTS); also elsewhere on the board
/DTR: C54.2, J1.1, J13.1 (Pin_1_1), U8.21 (D4/~DTR), U13.2 (DTR); also elsewhere on the board
/MRX: J1.2, R10.2, R52.1; also elsewhere on the board
/MTX: J1.3, R11.2, R54.1; also elsewhere on the board
/ft232/3v3_OUT: C12.1, J2.1 (Pin_1_1), JP1.1 (A), U13.17 (3V3OUT)
/ft232/+: R22.1, U13.15 (USBD+)
/ft232/-: R23.1, U13.16 (USBD-)
/ft232/CBUS_0: D1.1 (K), U8.12 (~TXLED), U13.23 (CBUS0)
/ft232/CBUS_1: D2.1 (K), U8.11 (~RXLED), U13.22 (CBUS1)
/ft232/CBUS_2: U13.13 (CBUS2)
/ft232/CBUS_3: R13.1, U8.15 (~PWREN), U13.14 (CBUS3)
/ft232/CBUS_4: U13.12 (CBUS4)
/ft232/DM_-: J3.2 (D-), R23.2, R50.1
/ft232/DP_+: J3.3 (D+), R22.2, R51.1
/ft232/FT_CTL: R73.2
/ft232/FT_DCD: J15.1 (Pin_1_1), U8.19 (D6/~DCD), U13.10 (DCD)
/ft232/FT_DSR: U8.20 (D5/~DSR)
/ft232/FT_EECS: U8.32 (EECS), U15.1 (CS)
/ft232/FT_EEDATA: R55.1, U8.2 (EEDATA), U15.3 (DI)
/ft232/FT_EESK: U8.1 (EESK), U15.2 (SCLK)
/ft232/FT_RESET: R57.2, R71.1, R72.2, U8.4 (~RESET)
/ft232/FT_RI: J16.1 (Pin_1_1), U8.18 (D7/~RI), U13.6 (RI)
/ft232/FT_RST: R18.2, R19.2, R21.2, U8.23 (D2/~RST), U13.19 (~RESET)
/ft232/FT_RTS: J8.1 (Pin_1_1), U13.3 (RTS)
/ft232/FT_TXD_EN: J18.1 (Pin_1_1), U8.16 (TXDEN)
/ft232/FT_XTIN: C15.1, U13.28 (OSCO), Y3.1
/ft232/FT_XTOUT: C16.1, U13.27 (OSCI), Y3.3
/ft232/MCLR: C9.1, J17.1 (Pin_1_1)
/ft232/PWR: C57.2, J20.1 (Pin_1_1), Q14.3, R9.1
/ft232/Reset: C54.1, J24.1 (Pin_1_1)
unnamed: D1.2 (A), R8.2
unnamed: D2.2 (A), R12.2
unnamed: D6.2 (A), R9.2
unnamed: J3.1 (VBUS), L1.1
unnamed: C47.1, J19.1 (Pin_1_1), Q14.1, R13.2, R24.1
unnamed: R55.2, U15.4 (DO)
unnamed: C67.1, U8.6 (3V3OUT)
unnamed: C11.1, R14.1, U8.30 (AVCC)
unnamed: R52.2, U8.25 (D0/TXD)
unnamed: R54.2, U8.24 (D1/RXD)
unnamed: R73.1, U8.14 (PWRCTL)
unnamed: R50.2, U8.8 (USBDM)
unnamed: R17.2, R51.2, U8.7 (USBDP)
unnamed: C66.1, U8.27 (XTIN), Y4.2
unnamed: C65.1, U8.28 (XTOUT), Y4.1
unnamed: R17.1, U8.5 (~RSTOUT)
unnamed: R56.2, U8.10 (~SLEEP)
unnamed: R11.1, U13.5 (RXD)
unnamed: R10.1, U13.1 (TXD)

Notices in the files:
README.md:
License: MIT
